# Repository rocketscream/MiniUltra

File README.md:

# Mini Ultra

An ultra low power Arduino compatible board based on the ATMega4808. The board is able to run from variety type of battery below and above it's 3.3V operating voltage. This allow batteries such as 2xNiMH, 3V CR123A, Li-Ion/Pol, 2 or 3 alkaline and LiFePO4 to be used. Board sleep at 3.7 uA with the on-chip real time counter (RTC) running.

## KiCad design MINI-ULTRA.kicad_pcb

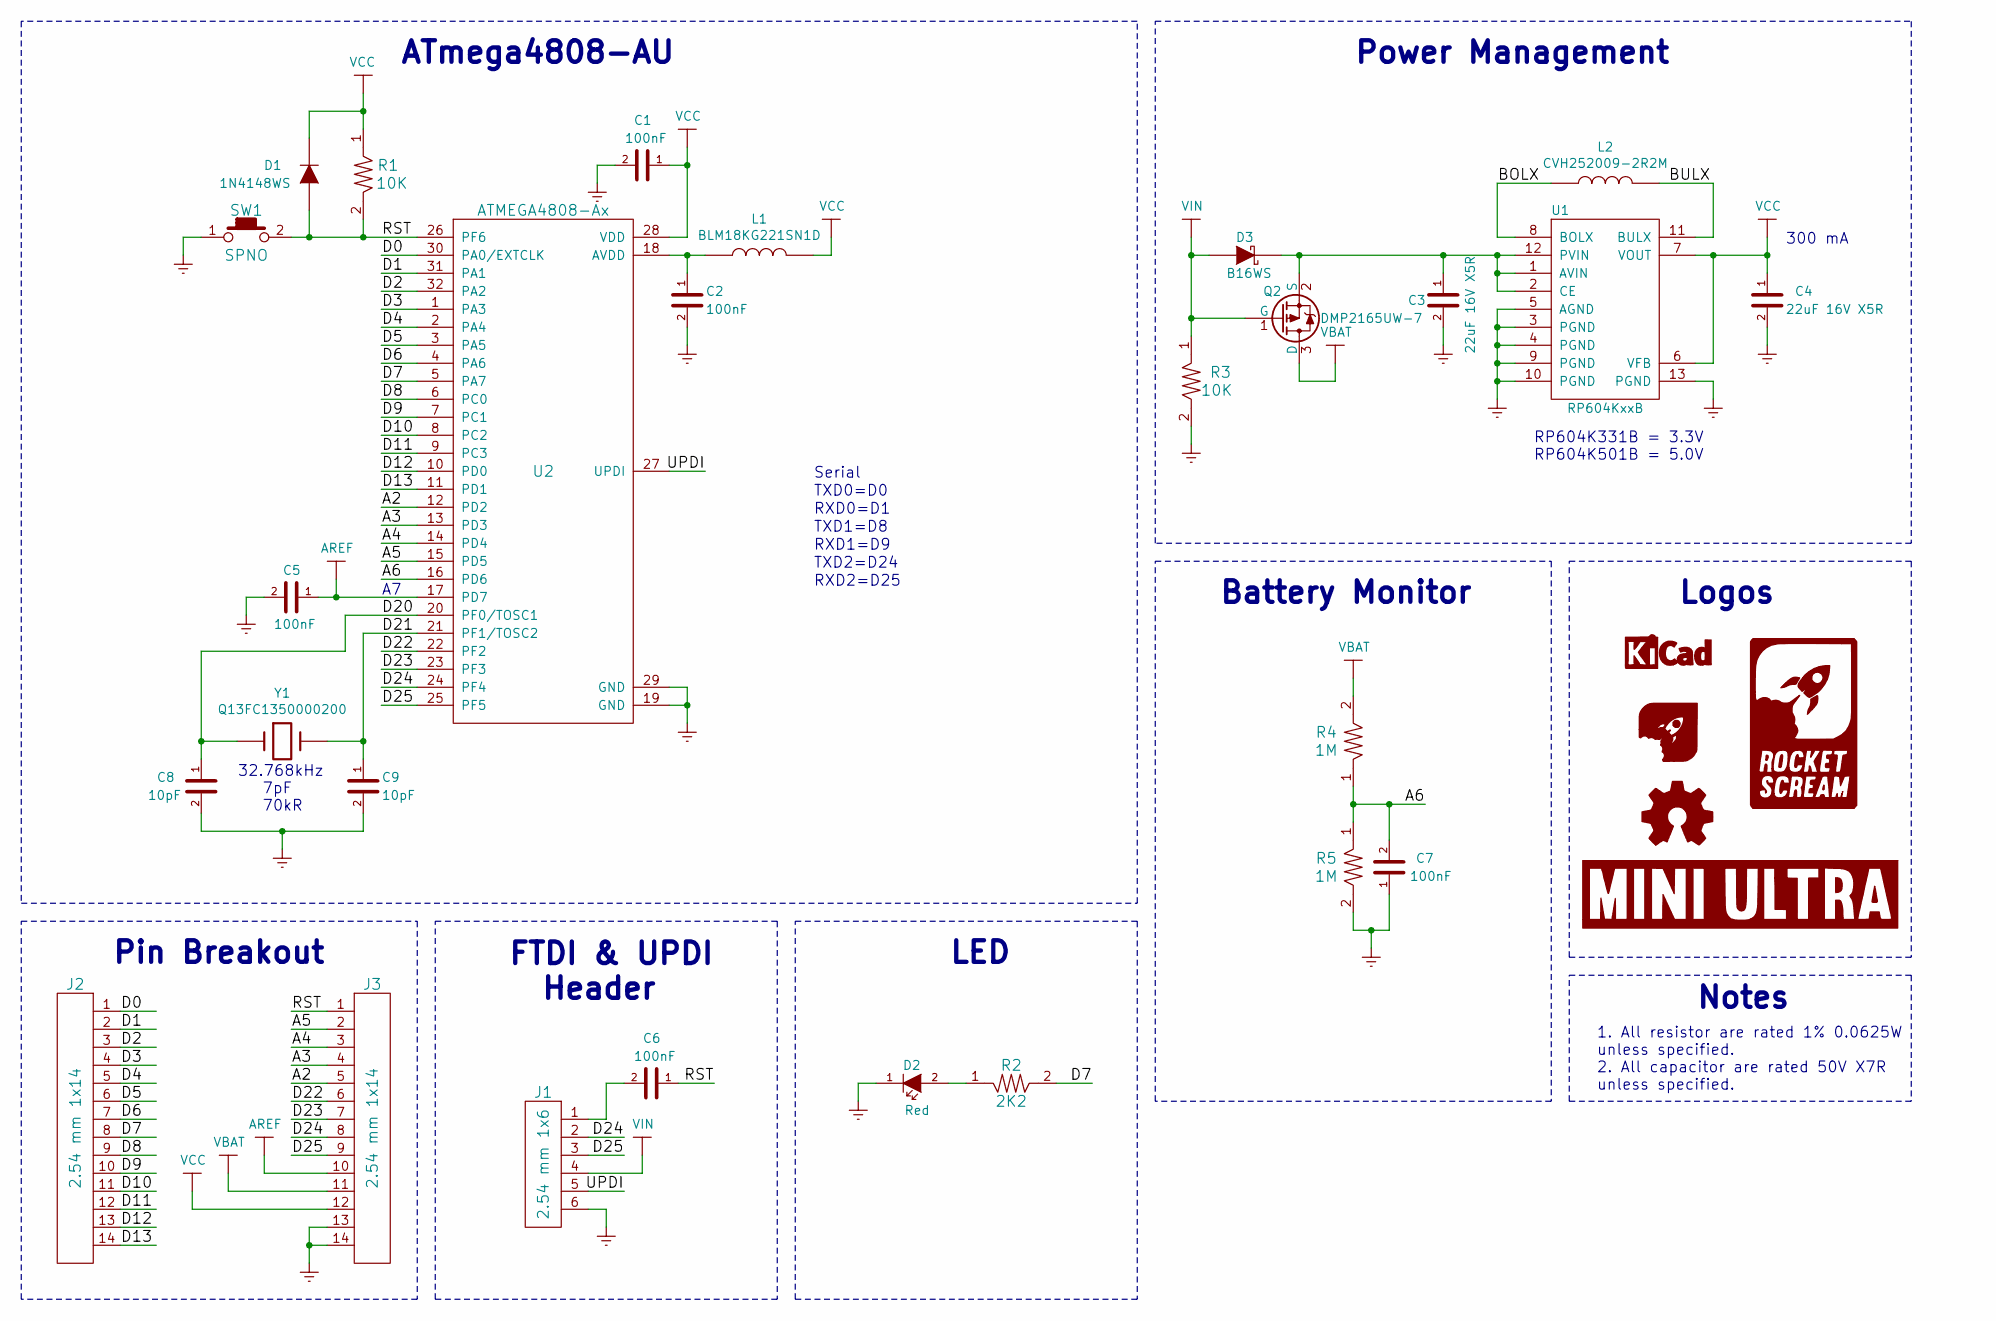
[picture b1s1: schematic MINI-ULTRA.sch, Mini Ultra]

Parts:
C1, C2, C5, C6, C7: 100nF; C_0603
C3, C4: 22uF 16V X5R; C_0805
C8, C9: 10pF; C_0603
D1: 1N4148WS; SOD-323
D2: Red; LED_0603
D3: B16WS; SOD-323
J1: 2.54 mm 1x6; HDR_1x6_Pitch2.54mm
J2, J3: 2.54 mm 1x14; HDR_1x14_Pitch2.54mm
L1: BLM18KG221SN1D; I_0603
L2: CVH252009-2R2M; I_2520
LOGO1: LOGO-KICAD; LOGO-KICAD_XXXSmall
LOGO2: LOGO-ROCKET-SCREAM-VERTICAL; LOGO-ROCKET-SCREAM_Vertical_XSmall
LOGO3: LOGO-ROCKET-SCREAM-WITHOUT-TEXT; LOGO-ROCKET-SCREAM_Without_Text_XXXXSmall
LOGO4: LOGO-OSHW; LOGO-OSHW_XXSmall
LOGO5: LOGO-MINI-ULTRA; LOGO-MINI-ULTRA_InvertedDualLineSmall
Q2: DMP2165UW-7; SOT-323
R1, R3: 10K; R_0603
R2: 2K2; R_0603
R4, R5: 1M; R_0603
SW1: SPNO; TS-107A
U1: RP604KxxB; DFN-12
U2: ATMEGA4808-Ax; TQFP-32_7x7mm_Pitch0.8mm
Y1: Q13FC1350000200; CRYSTAL-3215-2P

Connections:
/A2: J3.5, U2.12 (PD2)
/A3: J3.4, U2.13 (PD3)
/A4: J3.3, U2.14 (PD4)
/A5: J3.2, U2.15 (PD5)
/A6: C7.2, R4.1, R5.1, U2.16 (PD6)
/BOLX: L2.1, U1.8 (BOLX)
/BULX: L2.2, U1.11 (BULX)
/D0: J2.1, U2.30 (PA0/EXTCLK)
/D1: J2.2, U2.31 (PA1)
/D2: J2.3, U2.32 (PA2)
/D3: J2.4, U2.1 (PA3)
/D4: J2.5, U2.2 (PA4)
/D5: J2.6, U2.3 (PA5)
/D6: J2.7, U2.4 (PA6)
/D7: J2.8, R2.2, U2.5 (PA7)
/D8: J2.9, U2.6 (PC0)
/D9: J2.10, U2.7 (PC1)
/D10: J2.11, U2.8 (PC2)
/D11: J2.12, U2.9 (PC3)
/D12: J2.13, U2.10 (PD0)
/D13: J2.14, U2.11 (PD1)
/D20: C8.1, U2.20 (PF0/TOSC1), Y1.1
/D21: C9.1, U2.21 (PF1/TOSC2), Y1.2
/D22: J3.6, U2.22 (PF2)
/D23: J3.7, U2.23 (PF3)
/D24: J1.2, J3.8, U2.24 (PF4)
/D25: J1.3, J3.9, U2.25 (PF5)
/RST: C6.1, D1.2 (A), J3.1, R1.2, SW1.2, U2.26 (PF6)
/UPDI: J1.5, U2.27 (UPDI)
AREF: C5.1, J3.10, U2.17 (PD7)
GND: C1.2, C2.2, C3.2, C4.2, C5.2, C7.1, C8.2, C9.2, D2.1 (K), J1.6, J3.13, J3.14, R3.2, R5.2, SW1.1, U1.3 (PGND), U1.4 (PGND), U1.5 (AGND), U1.9 (PGND), U1.10 (PGND), U1.13 (PGND), U2.19 (GND), U2.29 (GND)
unnamed: C2.1, L1.1, U2.18 (AVDD)
unnamed: C3.1, D3.1 (K), Q2.2 (S), U1.1 (AVIN), U1.2 (CE), U1.12 (PVIN)
unnamed: C6.2, J1.1
unnamed: D2.2 (A), R2.1
VBAT: J3.11, Q2.3 (D), R4.2
VCC: C1.1, C4.1, D1.1 (K), J3.12, L1.2, R1.1, U1.6 (VFB), U1.7 (VOUT), U2.28 (VDD)
VIN: D3.2 (A), J1.4, Q2.1 (G), R3.1

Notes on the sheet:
Power Management
ATmega4808-AU
LED
1. All resistor are rated 1% 0.0625W unless specified. 2. All capacitor are rated 50V X7R unless specified.
Notes
Logos
FTDI & UPDI Header
Pin Breakout
RP604K331B = 3.3V RP604K501B = 5.0V
Battery Monitor
TXD2=D24
RXD2=D25
32.768kHz 7pF 70kR
TXD1=D8
RXD1=D9
TXD0=D0
RXD0=D1
Serial
300 mA

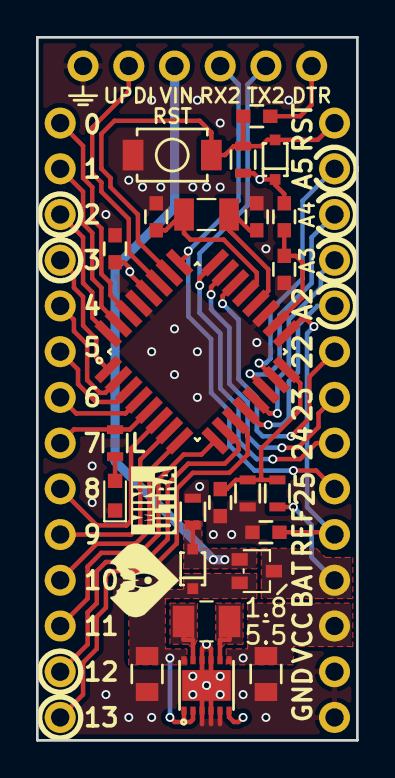
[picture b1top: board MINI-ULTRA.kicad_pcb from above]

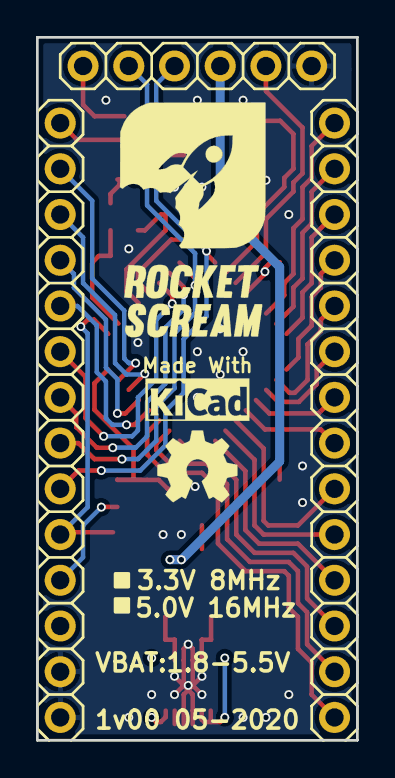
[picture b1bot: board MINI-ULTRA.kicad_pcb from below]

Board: 4 copper layers, 17.8 x 39.1 mm, 32 parts (6 on the bottom side), 38 nets.

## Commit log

2020-10-21 v1.00
